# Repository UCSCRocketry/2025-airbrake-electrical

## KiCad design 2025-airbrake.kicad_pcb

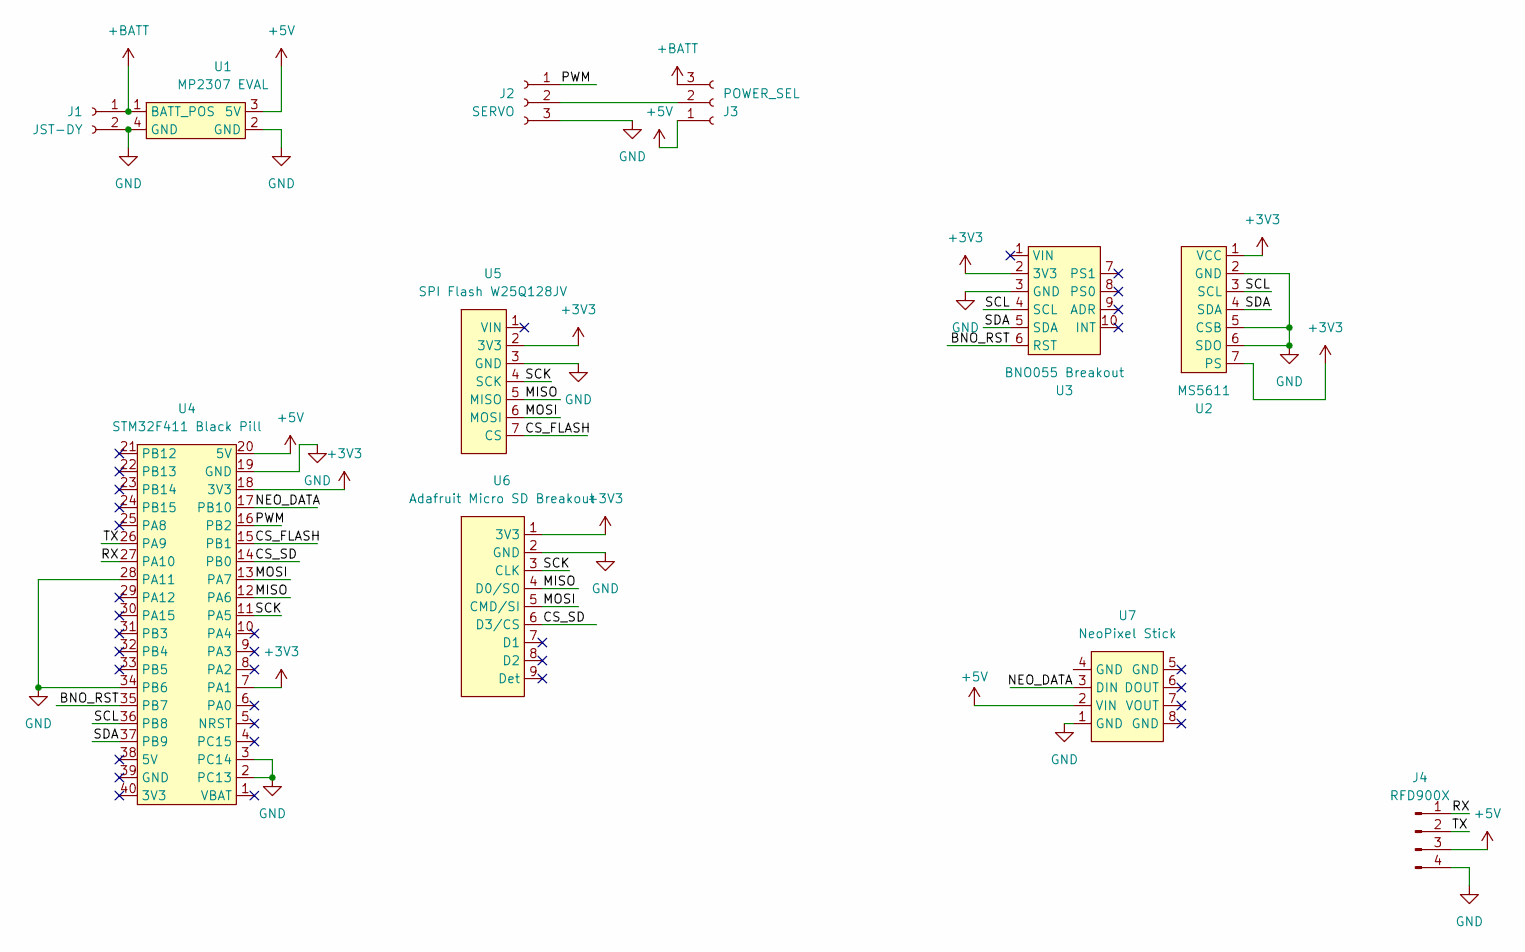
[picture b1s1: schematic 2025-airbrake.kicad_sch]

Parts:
J1: JST-DY; PinSocket_1x02_P2.54mm_Horizontal
J2: SERVO; PinHeader_1x03_P2.54mm_Horizontal
J3: POWER_SEL; PinHeader_1x03_P2.54mm_Horizontal
J4: RFD900X; PinHeader_1x04_P2.54mm_Horizontal
U1: MP2307 EVAL; PinHeader_2x02_P2.54mm_Vertical
U2: MS5611; PinSocket_1x07_P2.54mm_Vertical
U3: BNO055 Breakout; BNO055-Breakout
U4: STM32F411 Black Pill; STM32F411-Blackpill
U5: SPI Flash W25Q128JV; PinSocket_1x07_P2.54mm_Vertical
U6: Adafruit Micro SD Breakout; PinSocket_1x09_P2.54mm_Vertical
U7: NeoPixel Stick; NeoPixel-Stick

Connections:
+3V3: U2.1 (VCC), U2.7 (PS), U3.2 (3V3), U4.7 (PA1), U4.18 (3V3), U5.2 (3V3), U6.1 (3V3)
+5V: J3.1, J4.3, U1.3 (5V), U4.20 (5V), U7.2 (VIN)
+BATT: J1.1, J3.3, U1.1 (BATT_POS)
/BNO_RST: U3.6 (RST), U4.35 (PB7)
/CS_FLASH: U4.15 (PB1), U5.7 (CS)
/CS_SD: U4.14 (PB0), U6.6 (D3/CS)
/MISO: U4.12 (PA6), U5.5 (MISO), U6.4 (D0/SO)
/MOSI: U4.13 (PA7), U5.6 (MOSI), U6.5 (CMD/SI)
/NEO_DATA: U4.17 (PB10), U7.3 (DIN)
/PWM: J2.1, U4.16 (PB2)
/RX: J4.1, U4.27 (PA10)
/SCK: U4.11 (PA5), U5.4 (SCK), U6.3 (CLK)
/SCL: U2.3 (SCL), U3.4 (SCL), U4.36 (PB8)
/SDA: U2.4 (SDA), U3.5 (SDA), U4.37 (PB9)
/TX: J4.2, U4.26 (PA9)
GND: J1.2, J2.3, J4.4, U1.2 (GND), U1.4 (GND), U2.2 (GND), U2.5 (CSB), U2.6 (SDO), U3.3 (GND), U4.2 (PC13), U4.3 (PC14), U4.19 (GND), U4.28 (PA11), U4.34 (PB6), U5.3 (GND), U6.2 (GND), U7.1 (GND)
unnamed: J2.2, J3.2

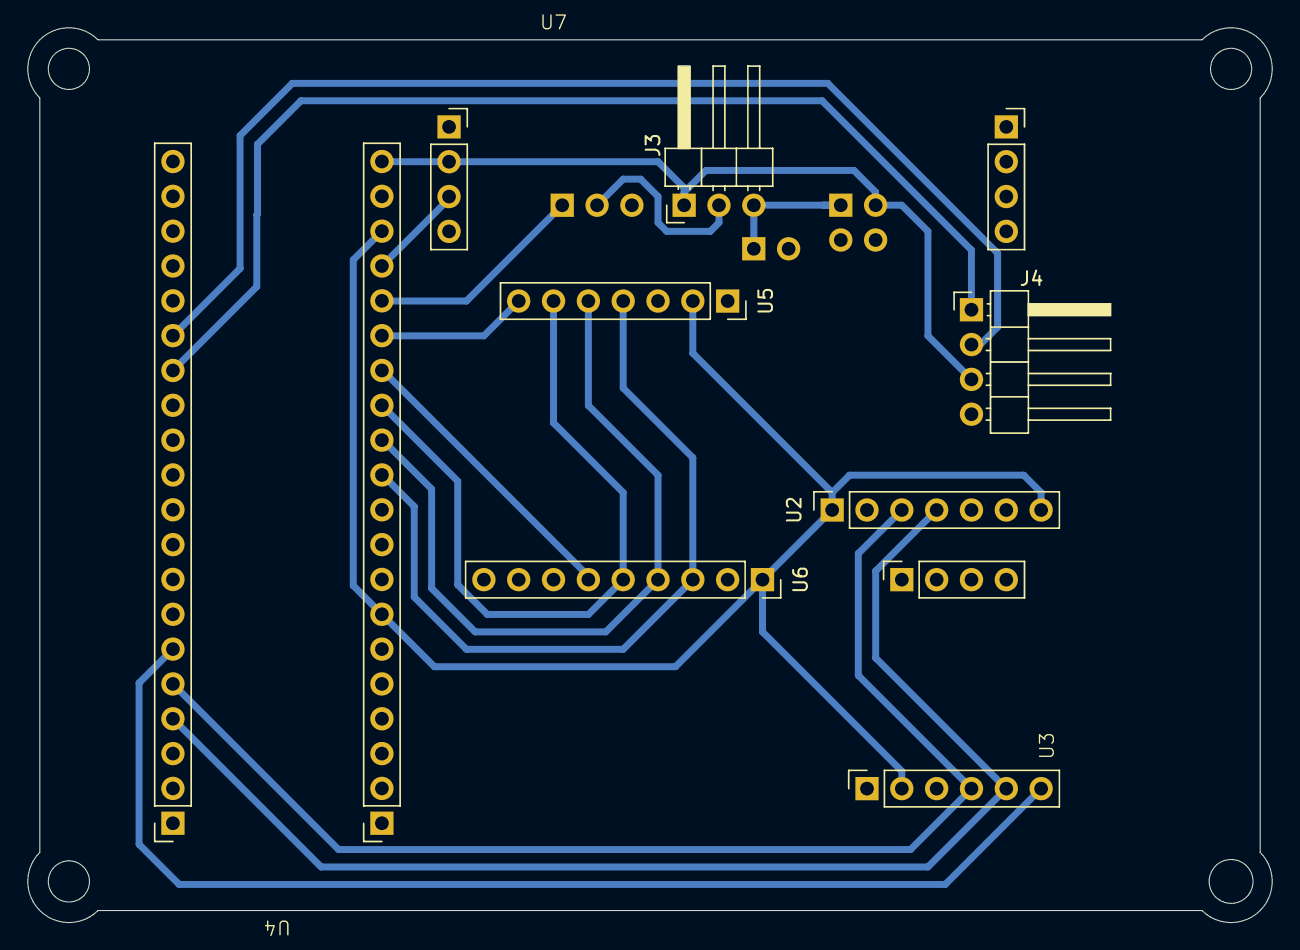
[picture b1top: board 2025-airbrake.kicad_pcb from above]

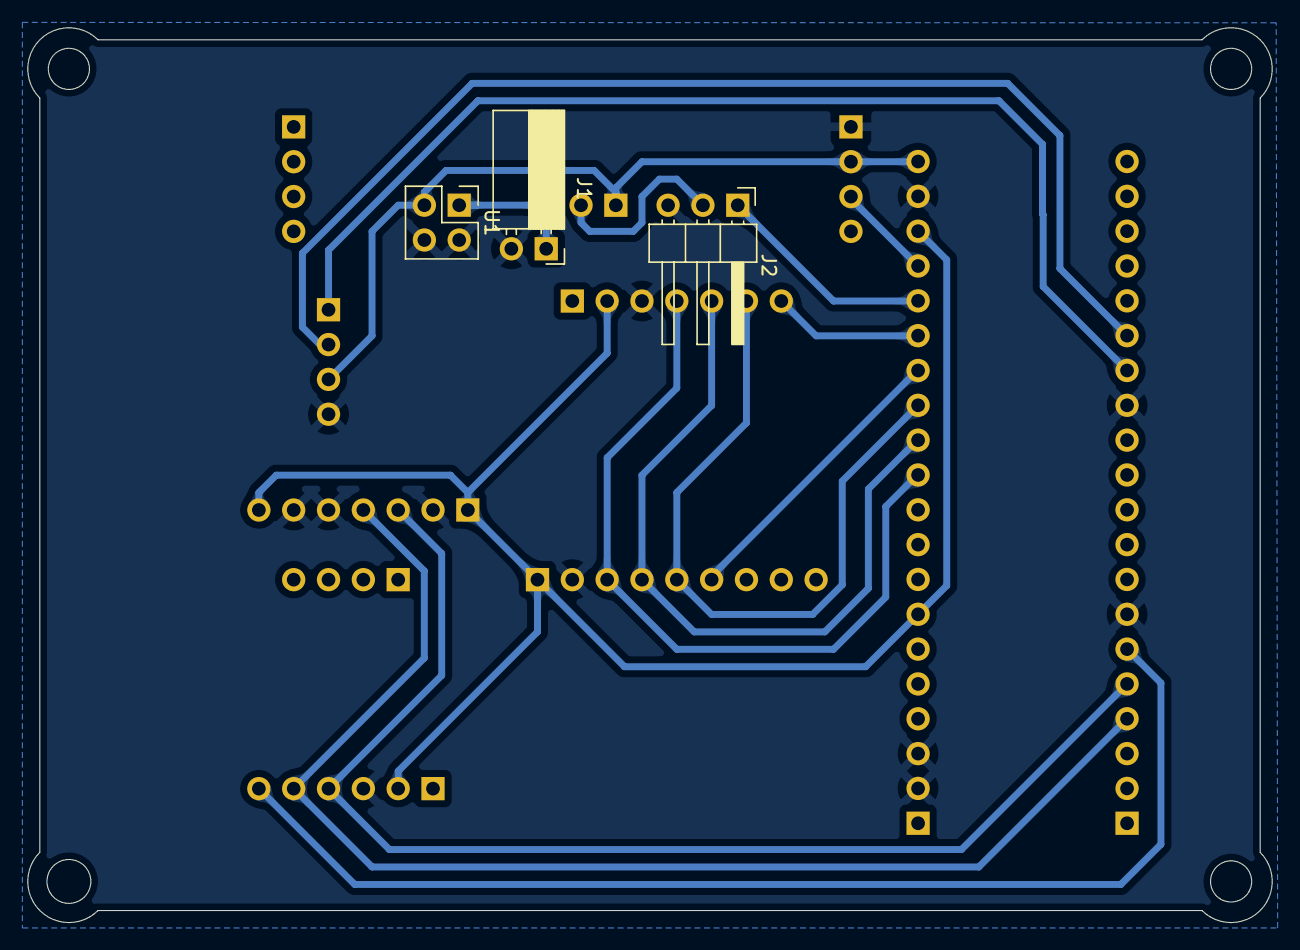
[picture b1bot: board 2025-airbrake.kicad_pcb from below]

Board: 2 copper layers, 90.8 x 65.3 mm, 11 parts (3 on the bottom side), 17 nets.

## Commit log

2025-10-20 Routing
2025-11-19 Added symbols and heiarchy
